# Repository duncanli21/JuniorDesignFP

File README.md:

# JuniorDesignFP
Final Project for Junior Design

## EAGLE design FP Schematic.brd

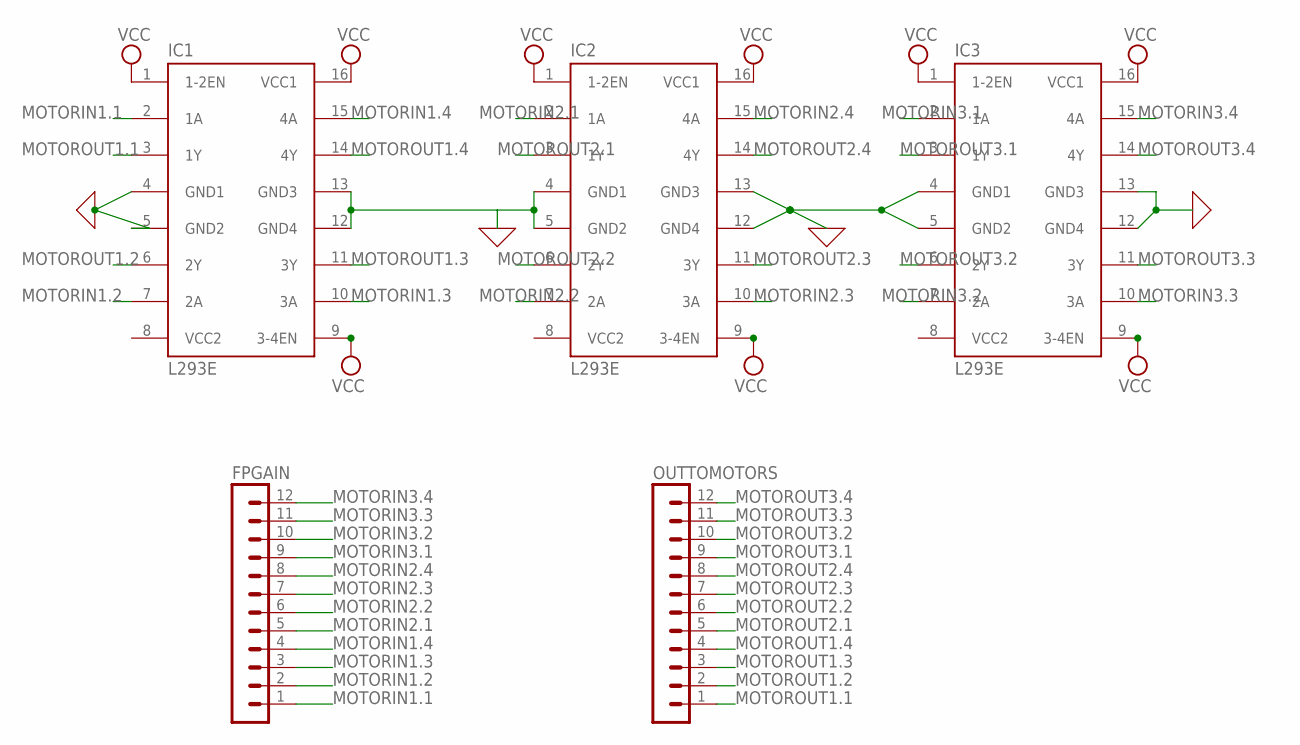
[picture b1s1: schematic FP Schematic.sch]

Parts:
FPGAIN: MA12-1
IC1, IC2, IC3: L293E; DIL16
OUTTOMOTORS: MA12-1

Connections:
0: IC1.4 (GND1), IC1.5 (GND2), IC1.12 (GND4), IC1.13 (GND3), IC2.4 (GND1), IC2.5 (GND2), IC2.12 (GND4), IC2.13 (GND3), IC3.4 (GND1), IC3.5 (GND2), IC3.12 (GND4), IC3.13 (GND3)
MOTORIN1.1: FPGAIN.1, IC1.2 (1A)
MOTORIN1.2: FPGAIN.2, IC1.7 (2A)
MOTORIN1.3: FPGAIN.3, IC1.10 (3A)
MOTORIN1.4: FPGAIN.4, IC1.15 (4A)
MOTORIN2.1: FPGAIN.5, IC2.2 (1A)
MOTORIN2.2: FPGAIN.6, IC2.7 (2A)
MOTORIN2.3: FPGAIN.7, IC2.10 (3A)
MOTORIN2.4: FPGAIN.8, IC2.15 (4A)
MOTORIN3.1: FPGAIN.9, IC3.2 (1A)
MOTORIN3.2: FPGAIN.10, IC3.7 (2A)
MOTORIN3.3: FPGAIN.11, IC3.10 (3A)
MOTORIN3.4: FPGAIN.12, IC3.15 (4A)
MOTOROUT1.1: IC1.3 (1Y), OUTTOMOTORS.1
MOTOROUT1.2: IC1.6 (2Y), OUTTOMOTORS.2
MOTOROUT1.3: IC1.11 (3Y), OUTTOMOTORS.3
MOTOROUT1.4: IC1.14 (4Y), OUTTOMOTORS.4
MOTOROUT2.1: IC2.3 (1Y), OUTTOMOTORS.5
MOTOROUT2.2: IC2.6 (2Y), OUTTOMOTORS.6
MOTOROUT2.3: IC2.11 (3Y), OUTTOMOTORS.7
MOTOROUT2.4: IC2.14 (4Y), OUTTOMOTORS.8
MOTOROUT3.1: IC3.3 (1Y), OUTTOMOTORS.9
MOTOROUT3.2: IC3.6 (2Y), OUTTOMOTORS.10
MOTOROUT3.3: IC3.11 (3Y), OUTTOMOTORS.11
MOTOROUT3.4: IC3.14 (4Y), OUTTOMOTORS.12
VCC: IC1.1 (1-2EN), IC1.9 (3-4EN), IC1.16 (VCC1), IC2.1 (1-2EN), IC2.9 (3-4EN), IC2.16 (VCC1), IC3.1 (1-2EN), IC3.9 (3-4EN), IC3.16 (VCC1)
VCC2: IC1.8 (VCC2), IC2.8 (VCC2), IC3.8 (VCC2)

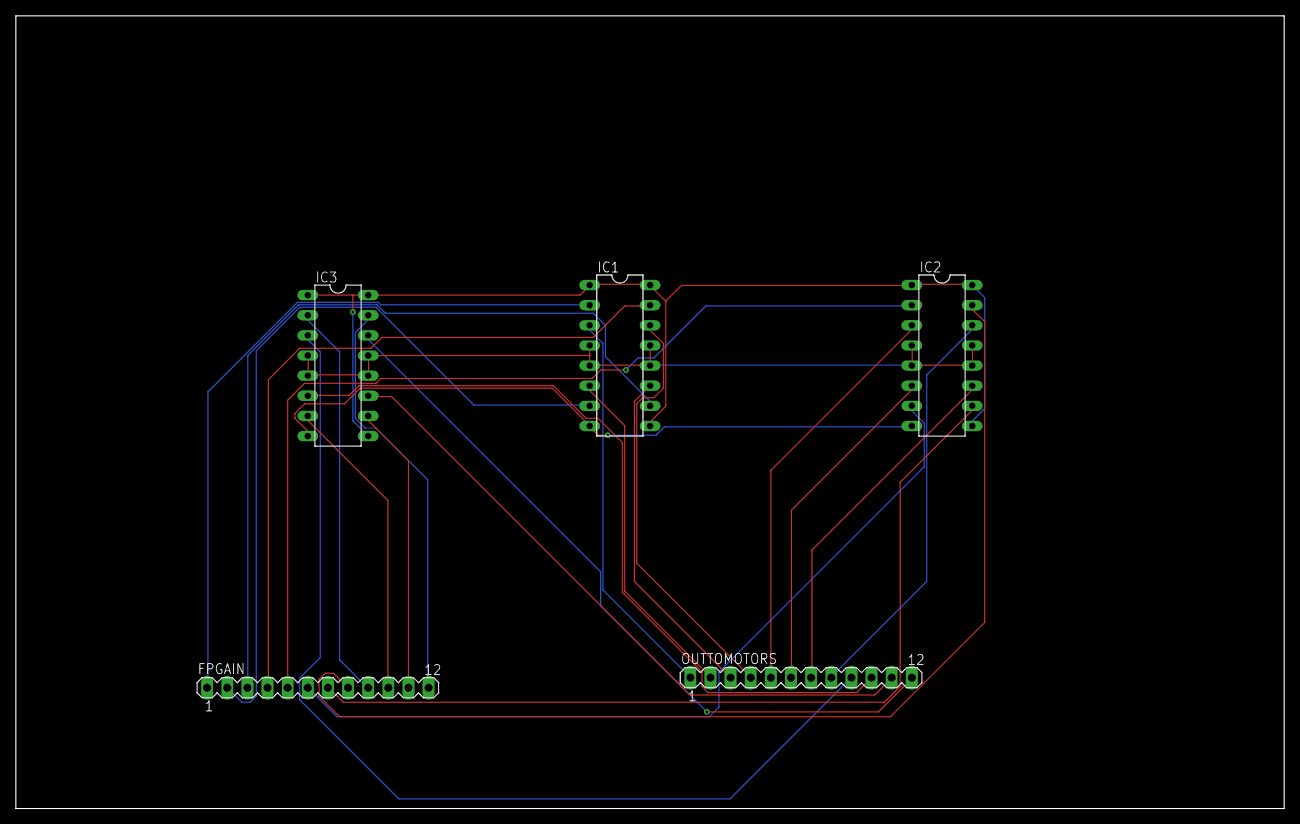
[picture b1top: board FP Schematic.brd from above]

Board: 2 copper layers, 160.0 x 100.0 mm, 5 parts (0 on the bottom side), 27 nets.

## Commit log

2020-01-15 Eagle Files
